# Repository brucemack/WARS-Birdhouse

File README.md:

WARS LoRa Birdhouse Project
===========================

Looking for a different way to tweet?  This project explores the potential of using low-cost/low-bandwidth LoRa radios to build simple mesh networks that can pass text messages around town.  Networks of this type could be useful for emergency communications or 
other applications that can take advantage of the fully-autonomous (carbon-neutral) nature of the birdhouse repeater stations. This 
project is being undertaken by members of the Wellesley Amateur Radio Society, W1TKZ.  The design is 
made available for amateur (non-commercial) purposes in the spirit of experimentation and knowledge sharing
amongst the ham community.  At the very least, we're creating homes for some lucky birds in our area.

Please contact Bruce MacKinnon (KC1FSZ) if you have technical questions.  I am 
interested in home-brew radio projects, many of which can be 
found [on my QRZ page](https://www.qrz.com/db/kc1fsz). 

The [project WIKI is located here](https://github.com/brucemack/WARS-Birdhouse/wiki).

Will this bird fly?  Let's find out!  

Publicity
=========

* This project is mentioned in an excellent new book called [Other Networks: A Radical Technology Sourcebook](https://www.amazon.com/Other-Networks-Radical-Technology-Sourcebook/dp/1944860657) written by Dr. Lori Emerson, Associate Professor of Media Studies, Founding Director of the Media Archaeology Lab, and Director of the Intermedia Art, Writing and Performance Program at the University of Colorado Boulder. I was flattered that Dr. Emerson considered this technology to be "radical" enough to be included in her book, but it's probably not as radical as some of the other technologies she describes including a faster-than-light communications network and a pasilalinic-sympathetic compass.
* An article about this project (co-authored with Dan Brown W1DAN) appears in the Club Station column of the July 2023 issue of [ARRL QST Magazine](https://www.arrl.org/qst). It was nice of the League to publish this.
* A nice Hackaday article [can be found here](https://hackaday.com/2022/04/09/lora-powered-birdhouses-enable-wireless-networking-when-the-internets-down/).  I found this article amusing given its implication that our network could be used as a backup when the Internet was down.  I've not tried streaming Netflix over LoRa, but I'm guessing the video quality won't be great. :-)
* The Zero Retries newsletter covered the project [in June of 2023](https://www.zeroretries.org/i/126932222/thoughts-on-amateur-radio-adjacent-technologies-lora). Steve Stroh N8GNJ does a nice job with this widely-read newsletter and I was honored to be called "woefully misinformed" and "shortsighted" in his article.  As Lindsay Lohan once said, there is no such thing as bad publicity!

Design Overview
================

Nodes on the network are autonomous, solar-powered birdhouses that each contain a +20dBm/100mW radio (Semtech SX1276).  These birdhouses will run 24x7 assuming reasonable weather conditions.  USB-connected desktop nodes are used to access the network from a computer via serial connection.  An internet gateway node is also 
under development. 

LoRa range experiments have been widely documented.  Your milage will vary considerably depending on terrain, 
station hight, etc. Testing shows that 1 km link ranges are reasonable in suburban areas. 

Birdhouse packaging was chosen in order to blend into the surroundings more easily.  We want this project to be environmentally friendly.

Low-power, solar design allows the birdhouses to be 100% autonomous.  This makes it relatively easy to install a repeater station in any location that has good sun exposure and good visibility to other stations. 

The desktop station model is powered by the USB connection, does not have the battery/solar components, but 
is identical to the birdhouse repeaters from an RF/firmware perspective.

The birdhouse is run by an ESP32 microcontroller at the moment, although this decision is under  consideration.  A more power-efficient STM32 prototype is being worked on.

Commodity components are being used to keep birdhouse costs to a minimum.  Our goal is to keep the node cost under $50 USD. 

The software supports a simple message routing protocol that allows packets to "hop" between houses to reach their final destination.  Other control packets are used to extract engineering data and to control 
message routing.

The 33cm ham band (902-928 MHz) is used given that this is an experimental technology and **is not FCC Part 15 certified** at the moment.  All 
nodes must be installed/operated by FCC licensed amateur/ham radio operators under Part 97 rules.

A proof-of-concept network of 5 stations has been constructed in Wellesley, MA.  Messages have been successfully routed back and forth across the entire mesh, including hops between birdhouses that were separated by approximately 1 kilometer.  Antenna height is important, as always.  The houses have been subjected to bad New England weather conditions including snow, ice, extended periods of cloudy weather and sub-zero temperatures.  It is an open question as to how the system will perform when our trees have leaves on them again!

A 15 node beta network is currently in the planning stages.  This includes upgrades of the hardware and firmware.

If you are interested in _high-speed_ mesh networks built using commercial hardware this project might not be your thing.  Please take a look at AREDN (https://www.arednmesh.org) instead.  The AREDN team is doing great work.

Architecture Overview
=====================

How Do I Access The Network?
============================

Users access the network using desktop stations that are fitted with a USB serial port.  The desktop station runs exactly the same firmware as the birdhouse repeater.  A serial command protocol is used to send and receive messages on the network.  The desktop stations have all of the required RF components and are full-fledged nodes on the network (with their own addresses).  Desktop nodes don't use the solar/battery installation since they can be powered from the USB port.

Currently users interact with the network using a conventional serial terminal running on a PC (ie. PUTTY or something similar).  No special software is required.  A Python desktop user interface is planned to improve ergonomics.  The serial commands are described in a later section.

The expectation is that users will install a birdhouse station at some 
advantageous location on their property in order to join the network and
increase the network coverage area.  This
means that the required line-of-sight for the desktop station is much less 
important - it's a "short hop" onto  the network.

The other option is to connect the desktop station to a quality antenna 
using a longer feed-line and avoid the need for two stations.  Either configuration 
is fine.

The packaging for the desktop station has not yet been finalized.  At the moment 
the parts are mounted on a block of wood, as pictured below.  A resonant vertical antenna
and USB cable are included with the package.

How Can I Get A Birdhouse?
==========================

Hardware/firmware is still being refined as part of a club project.  All firmware, KiCAD files, and woodworking
dimensions are available on this site for anyone who wants to build a birdhouse for themselves.

After our next hardware iteration (V2) is tested we will be making the components available in kit form.

If you live in a strategic location at high elevation and you would like a fully-assembled, tested station we will be happy to provide one free of charge. :-)

Please contact the network administrator to be assigned a node address on the network.

Do I Need To Be A Ham To Use The Network?
=========================================

Yes. The radio module we are using is not Part 15 certified 
so it must be run using Part 97 (amateur) rules.  We are currently doing research on a non-ham ISM Part 15 version of the network 
to make it easy for non-licensed users to join the fun.  If anyone has expertise in this area please add a comment to [the discussion this topic in GitHub](https://github.com/brucemack/WARS-Birdhouse/discussions/2).

Per FCC rules, Part 15 and Part 97 networks will not talk to each other.

Protocol Documentation
======================

The network runs on the 33cm (902-928 MHz) amateur band.  We are running on 906.5 MHz, which lies
in the digital portion of the ARRL band plan for 33cm.  According to the New England Spectrum Management Council (NESMC, https://www.nesmc.org/) 902 MHz band plan, this frequency is in the "mixed use" section of the band.  Our frequency has been registered in the NESMC database to ensure proper coordination with other uses of this band.

The LoRa message payload is documented here in compliance with FCC regulations.  There is no encryption 
used anywhere in the design.  The information contained here is all that a listener would need to interpret the messages.

The standard LoRa physical packet format is used.  Particulars on LoRa parameters:

* 125k bandwidth mode
* CRC enabled, 4/5 coding rate
* Explicit header mode is used
* LoRa spreading factor 9
* 12 symbol preamble

Here is a summary of the physical layer packet format from the Semtech documentation:

A much more detailed explanation of [the LoRa encoding can be found here](https://www.epfl.ch/labs/tcl/wp-content/uploads/2020/02/Reverse_Eng_Report.pdf).

The payload above contains a 36-byte header followed by a variable length packet format.  Particulars:

* 36-byte fixed size. 
* Version (PV) is 2 (at the moment).
* Packet type (PT) describes the nature/handling of the message.  More on types below.
* Packet ID (PID) is used for acknowledgement and duplicate packet elimination.  16-bit integer (little endian).
* Call signs are in ASCII format, padded with spaces as needed.
* Source/destination addresses are 16-bit integer (little endian).  More on addresses below.

### Station Addressing Scheme

Each station is assigned a 16-bit address. Some addresses have special significance:
* 0x0000: Not used
* 0x0001 through 0xffef: Used for normal stations on the network.
* 0xfff0 through 0xfffd: Un-routed stations used for administrative/maintenance purposes.
* 0xfffe: Gateway station to other meshes
* 0xffff: The broadcast address

### Packet Types

Packet types are interpreted as follows:
* 0: Not used
* 1: General acknowledgement packet, used for reliable delivery.
* 2: Station ID/beacon packet.
* 3: Ping request.
* 4: Ping response (pong).
* 5: Station engineering data request.
* 6: Station engineering data response.  
  * See below for details of response.
* 7: Network path test request.  
  * Stations will add their node ID and last-hop RSSI data to this message as it is routed through the network.
* 8: Network path test response.  
  * Stations will add their node ID and last-hop RSSI data to this message as it is routed through the network.
* 9: Set security seed.  Used to establish the seed used to validate privileged requests.
* 10: Set route request.  (A privileged operation)
* 11: Get route data request.
* 12: Get route data response.
* 13: Discover route request (FUTURE USE).
* 14: Discover route response (FUTURE USE).
* 15: Station reset request. (A privileged operation)
* 16: Set station clock request. (A privileged operation)
* 17: Reset engineering counters request.
* 18: Firmware update request (FUTURE USE, privileged)
* 19-31: (RESERVED)
* 32: Routine text traffic.
  * ASCII, free-text payload.  Variable size, max size is 128 bytes.
* 33: Priority/emergency text traffic.
  * ASCII, free-text payload.  Variable size, max size is 128 bytes.
* 34: Routine binary/data traffic.
  * Variable size, max size is 128 bytes.  *NO ENCRYPTION ALLOWED!*
* 35: Priority/emergency binary/data traffic.
  * Variable size, max size is 128 bytes.  *NO ENCRYPTION ALLOWED!*
* 36: Station alert.  Used for sounding audible alarms, etc.

### Acknowledgement/De-Duplication 

Most packet types are acknowledged on each hop.  Packet type 1 is used for this purpose.  Note that this 
doesn't mean that the acknowledgement reaches the original sender, it just means that each 
station will get an ACK to indicate that a packet has been handed off to the next station in 
the route path.

Acknowledgement packets (type 1) and Station ID packets (type 2) are not acknowledged.

Stations will maintain a counter for each node that is receives packet from.  Duplicate packets
will be discarded based on the Packet ID counter.  A window will be used to avoid confusion when 
the counter wraps.

#### Station Engineering Data Packet

This packet returns technical data that is used to monitor the state of 
a station.  Format is a follows:

* 0-1: Firmware version 
* 2-3: Battery voltage in mV
* 4-5: Panel voltage in mV
* 6-9: Uptime in seconds
* 10-13: Time (in seconds since the epoch)
* 14-15: Boot count
* 16-17: Sleep count 
* 18-19: Receive packet count 
* 20-21: Routing error count
* 22-23: Temperature (when option installed)
* 24-25: Humidity (when option installed)
* 26-27: Device class
  * 0: Unspecified
  * 1: WARS Desktop ESP32
  * 2: WARS Birdhouse ESP32
  * 3: WARS Mesh gateway STM32
  * 4: WARS Internet gateway STM32
  * 5: WARS Desktop STM32
  * 6: WARS Birdhouse STM32
* 28-29: Device revision
* 30-31: Wrong-node receive packet count 

2 byte and 4 byte integers are in little-endian format.

Hardware Overview (Electronics)
===============================

The birdhouse repeater prototype (external view):

The birdhouse repeater prototype (internal electronics view):

A tower-mounted birdhouse repeater prototype at the QTH of KC1FSZ:

A custom PCB (V2) has been developed to improve integration and to make things easier for kit builders without SMD soldering capability.  This board also provides an SMA connector to make antenna experimentation easier.

Hardware Notes
--------------
* Voltage readings are taken on solar panels and batteries.
* The V2 schematic can be found [here](https://github.com/brucemack/WARS-Birdhouse/blob/main/kicad/WARS%20Birdhouse%20V2.pdf).

Hardware Overview (Woodwork)
============================

Repeater nodes are packaged in a standardized birdhouse enclosure that was designed for easy assembly.  
Six pieces of wood are required.  Components are attached using wood screws.  The birdhouse is fully
functional for small bird species.    

The roof is sloped at a 32 degree angle according to the recommended optimal configuration for 
solar generation at 42 degrees North latitude where the initial network was deployed. The design
may need to be adjusted for other locations.  

The wood parts for the birdhouse repeater prototype:

A tree-mounted repeater prototype installed in a tree inside of a cloverleaf on-/off-ramp:

A repeater station mounted on the top of North Hill in Needham, MA.

Lumber Cut List:

* 1"x5" nominal stock (4.5" actual)
  * Sides: 6 1/2" max length with 32 degree mitre
* 1"x6" nominal stock (5.5" actual)
  * Back: 10" length
  * Bottom: 6" length
  * Roof: 7 1/4" length with 32 degree bevel on table saw.  (Set fence at 6 1/2")
  * Front: 3 3/4" max length with 32 degree bevel on table saw. Hole 1 1/2" diameter.  (Measure this peice using side and adjust fence accordindly).

**PLEASE USE CAUTION WHEN WORKING WITH POWER TOOLS!**

Software Overview
=================

The LoRa software is completely homebrew - no off-the-shelf drivers are being used.  This
means much more work, and much more learning.

All nodes support a serial interface for interacting with the network, but this is only connected for desktop nodes.  

The serial command processor is implemented using this [very good project](https://github.com/philj404/SimpleSerialShell) by Phil Jensen.

A static routing mechanism is being used at the moment.  The routing table for each node can be changed remotely.  Dynamic routing will be developed in a future phase.

Developer Information
=====================

Please see the [project WIKI](https://github.com/brucemack/WARS-Birdhouse/wiki) for information on development, IDE setup, etc.

Related Technology
==================

* AREDN (Amateur Radio Emergency Mesh Network): A very cool
system that leverages WIFI technology to create off-grid
IP networks that support emergency communications.  These guys are doing much higher speeds and 
are using much more sophisticated hardware.  The WARS Birdhouse project uses a different 
wireless technology and is not interoperable with the ARDEN system.  See https://www.arednmesh.org. 
* LoRaHAM (https://github.com/travisgoodspeed/loraham): A great open-source project that explored some similar territory.  The project appears to be inactive at this time.
* LoRaWAN: A cool system that uses LoRa stations organized in a star topology.  The hub of each star is a gateway to the public internet.  This technology uses encryption and is not legal for amateur projects. 
* DASH7 wireless network (https://en.wikipedia.org/wiki/DASH7).  Uses encryption, so not good for Part 97, but interesting nonetheless.  

Reference Material
==================

* Radio Mobile by VE2DBE: https://www.ve2dbe.com/english1.html is a great program for understanding local-area/LOS propagation. 
* The Ubiquity Link Planner is very helpful for understanding land features between 
potential station sites: https://link.ui.com/#.2q
* LoRa rules, regulations, and terminology: https://lora.readthedocs.io/en/latest/#rules-and-regulations
* Reference for LoRa radio module (RFM95W): https://www.hoperf.com/modules/lora/RFM95.html
* LoRa Modulation Information: https://www.frugalprototype.com/wp-content/uploads/2016/08/an1200.22.pdf
* Reference for 18650 battery: https://cdn.sparkfun.com/datasheets/Prototyping/ICR18650%202600mAH%20datasheet.pdf
* Reference for LDO Voltage Regulator: https://ww1.microchip.com/downloads/en/DeviceDoc/MCP1700-Low-Quiescent-Current-LDO-20001826E.pdf
* Reference for STM32L031 microcontroller: https://www.st.com/resource/en/datasheet/stm32l031k6.pdf
* STM32L0 hardware design guide: https://www.st.com/resource/en/application_note/an4467-getting-started-with-stm32l0xx-hardware-development-stmicroelectronics.pdf
* Reference for the ESP32 D1 Mini: https://wiki.csgalileo.org/_media/projects/internetofthings/d1_mini_esp32_-_pinout.pdf
* An article on correcting non-linearity in the ESP32 AD converter: https://github.com/e-tinkers/esp32-adc-calibrate
* Datasheet for the W5500 which is used to create the bridge to an IP network: https://cdn.sparkfun.com/datasheets/Dev/Arduino/Shields/W5500_datasheet_v1.0.2_1.pdf
* A very interesting paper talking about the reverse-engineering of the LoRa physical layer: https://www.epfl.ch/labs/tcl/wp-content/uploads/2020/02/Reverse_Eng_Report.pdf

Detailed Parts List
-------------------
(To follow)

Hookup Notes
------------

Column 1

Row 0 - GND
Row 1 - Supply GND
Row 2 - IO33 (Battery Voltage Sense)
Row 3 - IO34 (Panel Voltage Sense)
Row 4 - Supply +VCC
Row 5 - Pannel
Row 6 - Pannel
Row 7 - +3.3V

Column 2

Row 0 
Row 1
Row 2 - IO19 (SPI MISO)
Row 3 - IO23 (SPI MOSI)
Row 4 - IO18 (SPI SCK)
Row 5 - IO5  (SPI NSS)
Row 6 - IO26 (Radio RST)
Row 7 - IO4  (Radio DIO0) 

Areas for Further Experimentation
=================================

Hardware 2.0 (In Process)
-------------------------
* Fully integrated PCB using surface mount components
* Switch to a ultra-low-power microprocessor: STM32L031
* SMA connector for more robust antenna experimentation

Hardware (Future)
-----------------
* Replace the linear regulator with a boost converter to improve battery usage.
* Complete the packaging of the birdhouse to ensure weatherproofing and full compatibility with avian residency.
* Cheaper antennas.
* Gain antennas for longer distance links.
* RF switch to allow dynamic switching between two antennas.  This might facilitate A/B testing, or possibly stations that have a directional/gain antenna for trunking and an omni-directional antenna for local access.
* A hand-held station with an LCD RSSI display for scouting potential station locations.

Software
--------
* Improved power efficiency using more aggressive sleeping.  Leverage the SX1276 receive interrupt or channel activity detection (CAD) interrupt to allow the system to sleep during periods of inactivity.
* Dynamic route discovery. At the moment the routes are static, but they can be modified over-the-air.
* Store and forward for times when a node is offline.
* Message sequence to avoid duplicate delivery.
* Network time synchronization.
* A more user-friendly desktop application written in Python.  This will make it easer for casual users of the work.
end-users to interact with the network.
* Network security.
* Over-the-air (OTA) software upgrades.

Relevant FCC Regulations/Notes
==============================

* Part 97.311 Defines spread-spectrum (SS) rules.
* Part 97.303 (N) Defines rules for the 33cm band.  Basically, hams must share the band with other services.  There are also geographical restrictions in Texas, New Mexico, Colorado, and Wyoming.
* Part 97.309 (B) Talks about unspecified data emission codes.  Basically, all formats need to be clearly documented. See above. 
* This firm does certification and [provides a detailed guide on the certification process](https://www.sunfiretesting.com/LoRa-FCC-Certification-Guide/).  

Copyright Information 
=====================

Copyright (C) 2023 - Bruce MacKinnon KC1FSZ

This work is covered under the terms of the GNU Public License (V3).  Please consult the 
LICENSE file for more information.  

This work is being made available for non-commercial use by the amateur radio community. Redistribution, commercial use or sale of any part is prohibited.

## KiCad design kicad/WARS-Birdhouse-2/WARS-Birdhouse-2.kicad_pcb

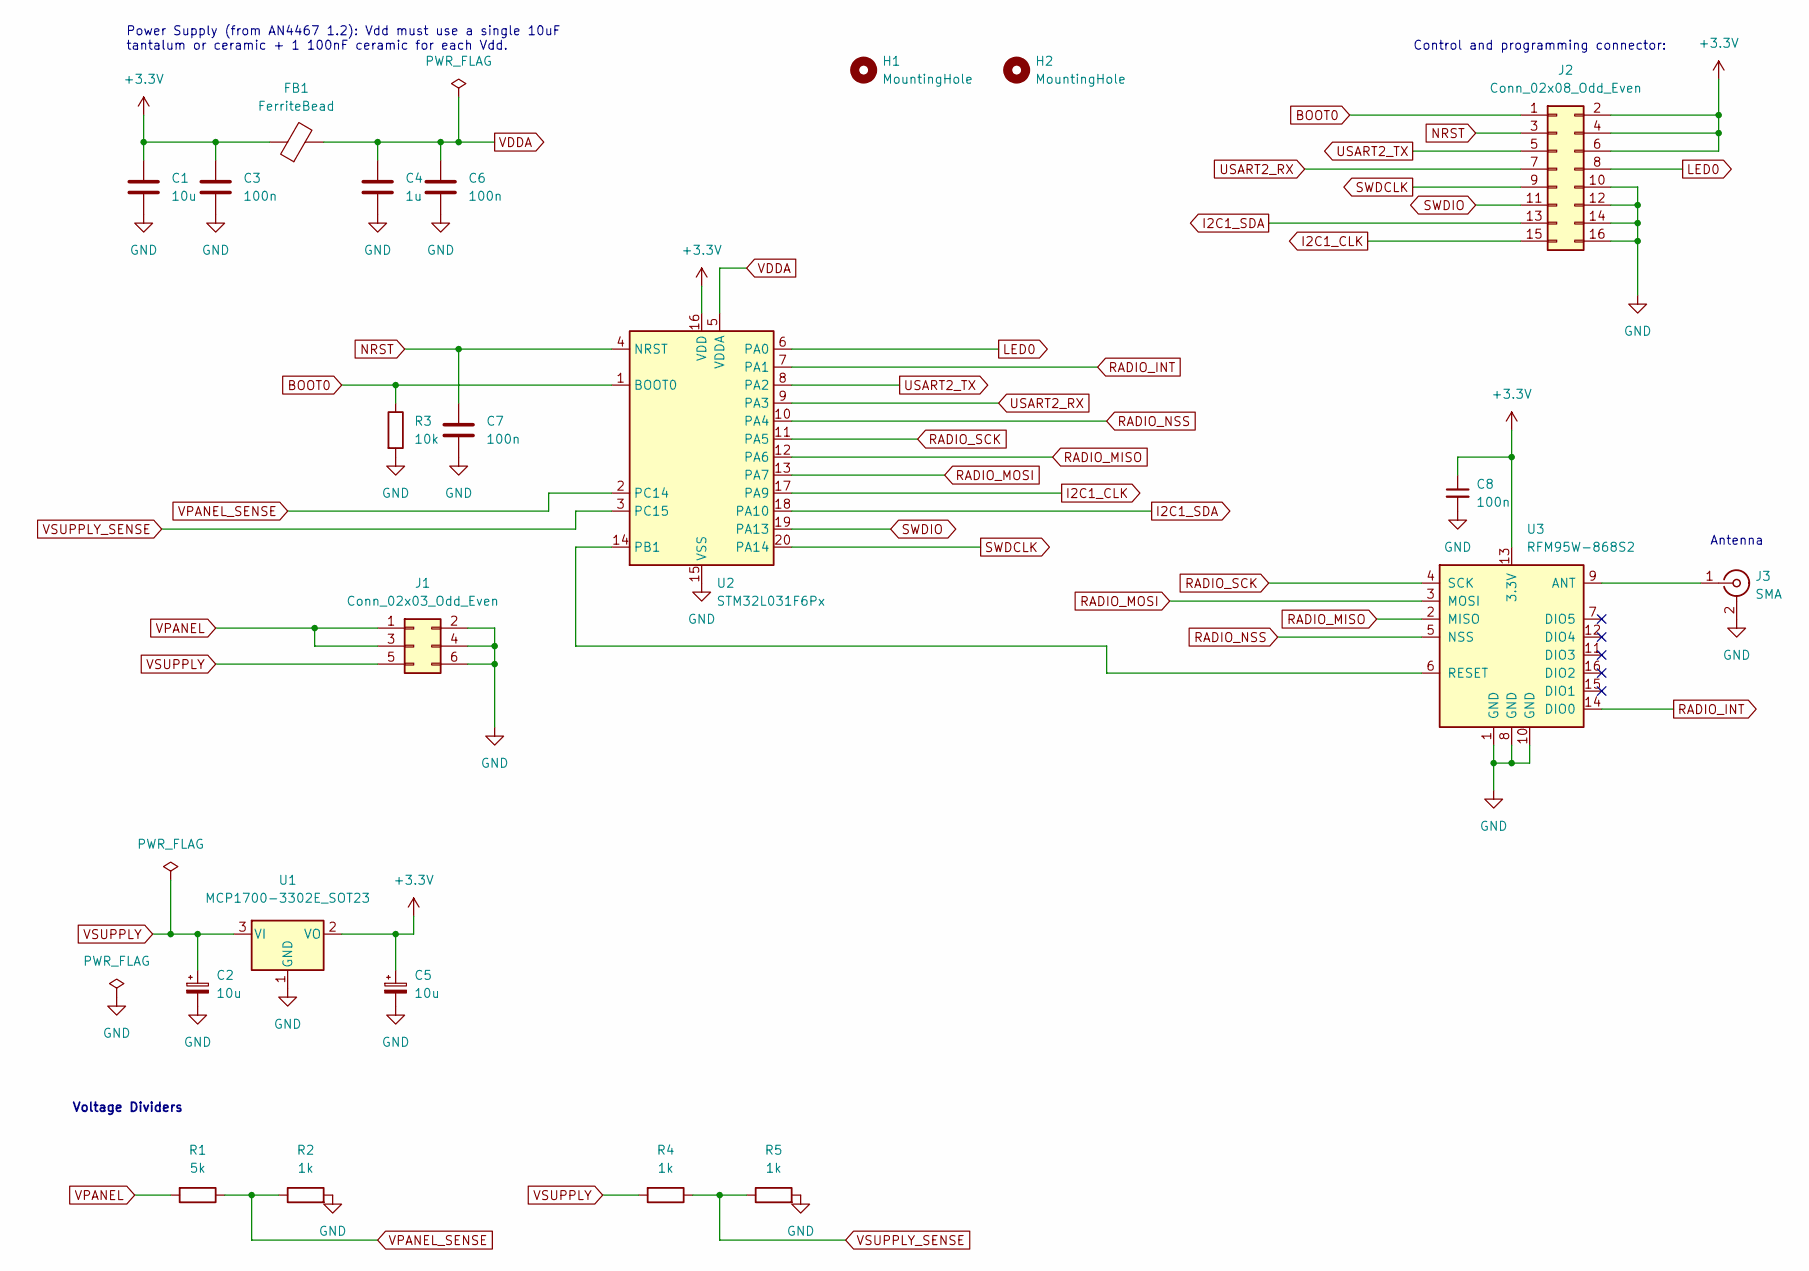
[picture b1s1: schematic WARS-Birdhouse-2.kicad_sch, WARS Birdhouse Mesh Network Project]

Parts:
C1: 10u; CP_EIA-3216-10_Kemet-I_Pad1.58x1.35mm_HandSolder
C2, C5: 10u; CP_Elec_4x5.4
C3, C6, C7, C8: 100n; C_0805_2012Metric_Pad1.18x1.45mm_HandSolder
C4: 1u; C_0805_2012Metric_Pad1.18x1.45mm_HandSolder
FB1: FerriteBead; C_0805_2012Metric_Pad1.18x1.45mm_HandSolder
H1, H2: MountingHole; MountingHole_4mm
J1: Conn_02x03_Odd_Even; PinHeader_2x03_P2.54mm_Vertical
J2: Conn_02x08_Odd_Even; PinHeader_2x08_P2.54mm_Vertical
J3: SMA; SMA_Amphenol_132134_Vertical
R1: 5k; R_0805_2012Metric_Pad1.20x1.40mm_HandSolder
R2, R4, R5: 1k; R_0805_2012Metric_Pad1.20x1.40mm_HandSolder
R3: 10k; R_0805_2012Metric_Pad1.20x1.40mm_HandSolder
U1: MCP1700-3302E_SOT23; SOT-23
U2: STM32L031F6Px; TSSOP-20_4.4x6.5mm_P0.65mm
U3: RFM95W-868S2; HOPERF_RFM9XW_SMD

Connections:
+3V3: C1.1, C3.1, C5.1, C8.1, FB1.1, J2.2, J2.4, J2.6, U1.2 (VO), U2.16 (VDD), U3.13 (3.3V)
BOOT0: J2.1, R3.1, U2.1 (BOOT0)
GND: C1.2, C2.2, C3.2, C4.2, C5.2, C6.2, C7.2, C8.2, J1.2, J1.4, J1.6, J2.10, J2.12, J2.14, J2.16, J3.2 (Ext), R2.2, R3.2, R5.2, U1.1 (GND), U2.15 (VSS), U3.1 (GND), U3.8 (GND), U3.10 (GND)
I2C1_CLK: J2.15, U2.17 (PA9)
I2C1_SDA: J2.13, U2.18 (PA10)
LED0: J2.8, U2.6 (PA0)
NRST: C7.1, J2.3, U2.4 (NRST)
unnamed: J3.1 (In), U3.9 (ANT)
unnamed: U2.14 (PB1), U3.6 (RESET)
RADIO_INT: U2.7 (PA1), U3.14 (DIO0)
RADIO_MISO: U2.12 (PA6), U3.2 (MISO)
RADIO_MOSI: U2.13 (PA7), U3.3 (MOSI)
RADIO_NSS: U2.10 (PA4), U3.5 (NSS)
RADIO_SCK: U2.11 (PA5), U3.4 (SCK)
SWDCLK: J2.9, U2.20 (PA14)
SWDIO: J2.11, U2.19 (PA13)
USART2_RX: J2.7, U2.9 (PA3)
USART2_TX: J2.5, U2.8 (PA2)
VDDA: C4.1, C6.1, FB1.2, U2.5 (VDDA)
VPANEL: J1.1, J1.3, R1.2
VPANEL_SENSE: R1.1, R2.1, U2.2 (PC14)
VSUPPLY: C2.1, J1.5, R4.2, U1.3 (VI)
VSUPPLY_SENSE: R4.1, R5.1, U2.3 (PC15)

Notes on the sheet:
Antenna
Voltage Dividers
Control and programming connector:
Power Supply (from AN4467 1.2): Vdd must use a single 10uF tantalum or ceramic + 1 100nF ceramic for each Vdd.

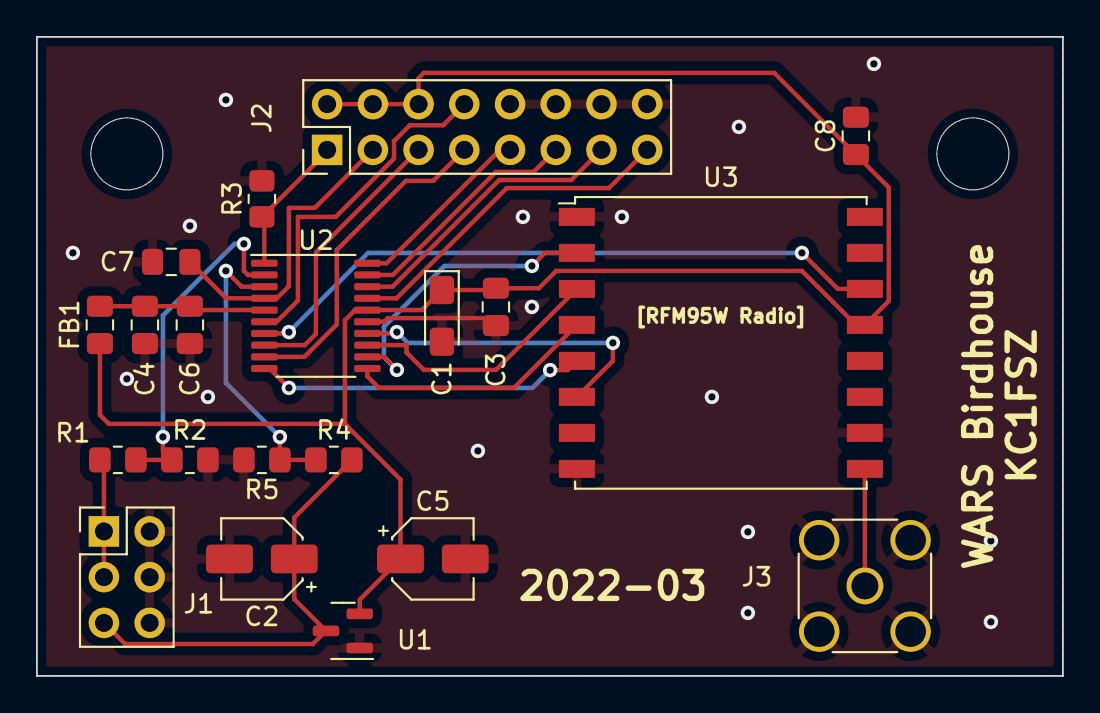
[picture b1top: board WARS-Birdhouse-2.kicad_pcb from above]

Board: 2 copper layers, 57.0 x 35.5 mm, 22 parts (0 on the bottom side), 23 nets.

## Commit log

2021-11-27 Routing working
2021-12-18 Added RSSI
2021-12-18 Added Watchdog
2021-12-18 Added uptime/boot count
2021-12-19 Changed type numbers, added the abilty to generate an ACK
2021-12-20 Working on adding the ability to wait for ACK
2021-12-26 Implemented ACK/retry
2021-12-27 Removed hard-coding, routing now stored in NVRAM
2021-12-27 Added blink command
2021-12-27 Added batterly level and low power checking
2021-12-27 Factored out SPI code
2021-12-28 Version 14 - Experimenting with alternate tokenizers
2021-12-28 Version 15 - Adjusted power
2021-12-28 Version 16 - Added TEXT command
2021-12-28 Version 18
2021-12-30 Version 20 - Added MAC address, radio sleep
2021-12-30 Added documentation
2022-01-06 Changed to a formal timer class
2022-01-16 Working on batteries
2022-01-16 Turned LNA to +150%, forgotten before
2022-01-16 Strings
2022-01-16 Review modem settings
2022-02-24 Improved docs
2022-02-26 Added panel voltage
2022-02-26 Added the ability to control the routing table remotely
2022-02-27 Working on remote access to routing table
2022-02-27 Moving to release 27 after fix to the shell (defect #28)
2022-03-04 Corrected a bug with deep sleep timer, added REM per Charlie's suggestion
2022-03-05 Added pictures
2022-03-05 Images
2022-03-06 Doc update
2022-03-08 Working on docs
2022-03-10 Working on 29 - allow sleep when receiving
2022-03-11 Docs
2022-03-12 Added resetcounter command
2022-03-12 Updated docs
2022-03-14 Docs update
2022-03-15 Added build docs
2022-03-16 Create LICENSE
2022-03-16 Docs improve
2022-03-30 Docs, licenses
2022-03-30 Image
2022-03-30 Comments from W1DAN
2022-03-31 Work in process, new packet format.
2022-03-31 Working on improving circulate buffer
2022-03-31 Added KiCAD files
2022-03-31 Adding unit tests
2022-03-31 Unit tests
2022-04-01 Restructuring
2022-04-02 Working on V2
2022-04-02 working
2022-04-02 Unit tests passing for OPM
2022-04-02 ackRequired() changes
2022-04-02 Working on message processor
2022-04-02 Working on MP
2022-04-02 Workig on MP
2022-04-03 Improving the unit test
2022-04-03 Added filter for messages targeted at a different node.
2022-04-03 Added license info
2022-04-03 Refactored timeotu
2022-04-03 Testing retry
2022-04-03 Testing timeout
2022-04-03 Testing
2022-04-03 Added Configiration interface
2022-04-03 Working on commands
2022-04-03 Working on unit test
2022-04-03 Reset working
2022-04-07 Added CallSign class
2022-04-07 Adding station config
2022-04-07 Configuration testing?
2022-04-07 Working on test cases
2022-04-07 Test cases
2022-04-09 Refactoring for V2
2022-04-09 Refactoring V2
2022-04-09 Info command working
2022-04-09 Set route working
2022-04-09 Routing table work
2022-04-09 Refactor/cleanup
2022-04-10 Working on boot count/sleep count
2022-04-10 Cleaning up compile issues
2022-04-11 Added reference to DASH7
2022-04-11 Compiling V2
2022-04-11 Further clean-up for V2
2022-04-13 Added links
2022-04-14 Added call sign to info read-out
2022-04-14 Resolved some NVRAM problems
2022-04-14 Reference to LoRa encoding
2022-04-14 Cleaned up unit tests, added callsign to text messags
2022-04-14 Added a command to request station engineering data
2022-04-14 Added a timeout for TX
2022-04-14 Corrected a problem with text
2022-04-15 Node 5 working
2022-04-15 Added message processing counters, added echo routing capability
2022-04-15 Added passcode, clean up
2022-04-15 Preparing for V2 end-to-end test
2022-04-15 Addressed defects with routing control
2022-04-15 Logging cleanup
2022-04-15 Workig on idle feature
2022-04-15 Fixed bug with passcode
2022-04-16 Improving logs
2022-04-16 Links to new WIKI
2022-04-16 Renamed the sketch to station
2022-04-17 Added retry ignore, added CAD, added RSSI on EDR packet
2022-04-17 Added timeout on retry ignore
2022-04-17 Merged V2->main, V2 working
2022-04-17 Formatting cleanup, reset bug
2022-04-18 Added command mode, text format
2022-04-18 added station id timer
2022-04-18 Cleaned up the periodic station ID
2022-04-18 Addressed RSSI defect
2022-04-24 Adjusted TX timeout
2022-04-24 Added pins
2022-05-07 Working on event loop
2022-05-07 Cleaned up errors
2022-05-07 Added state display
2022-06-02 Version 49
2022-06-11 Added reset when radio is in wrong state
2022-06-26 Added Bluetooth option
2022-08-27 New doc
2022-08-27 New slides
2022-10-22 Added docs
2023-10-20 Clarified FCC Part 15 certification
2025-06-24 Added book link

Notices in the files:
README.md:
Copyright Information:
Copyright (C) 2023 - Bruce MacKinnon KC1FSZ
This work is covered under the terms of the GNU Public License (V3).  Please consult the
LICENSE file for more information.
This work is being made available for non-commercial use by the amateur radio community. Redistribution, commercial use or sale of any part is prohibited.
kicad/WARS-Birdhouse-2/WARS-Birdhouse-2.kicad_sch:
COPYRIGHT (C) 2022 - Bruce MacKinnon
